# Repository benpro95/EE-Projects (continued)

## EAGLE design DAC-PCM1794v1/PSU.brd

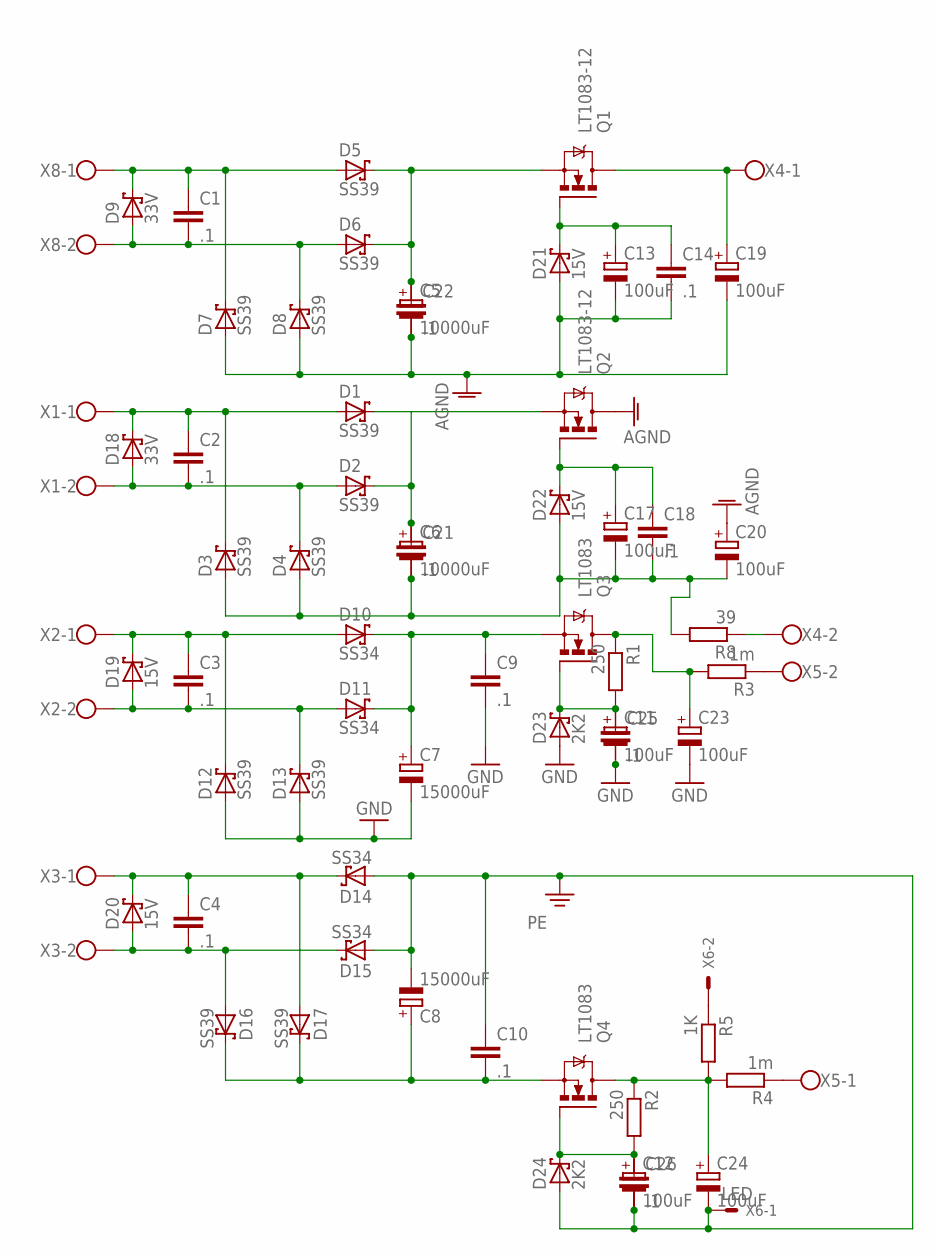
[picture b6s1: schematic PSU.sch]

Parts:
C1, C2, C3, C4: .1; C075-042X103
C5, C6: 10000uF; EB25D
C7, C8: 15000uF; EB25D
C9, C10, C14, C18, C21, C22, C25, C26: .1; C1210K
C11, C12, C13, C17, C19, C20, C23, C24: 100uF; E5-10,5
D1, D2, D3, D4, D5, D6, D7, D8, D12, D13, D16, D17: SS39; SMC
D9, D18: 33V; SMB
D10, D11, D14, D15: SS34; SMC
D19, D20, D21, D22: 15V; SMB
D23, D24: 2K2; SMB
Q1, Q2: LT1083-12; TO-247AD-H
Q3, Q4: LT1083; TO-247AD-H
R1, R2: 250; R1210
R3, R4: 1m; 0309/12
R5: 1K; R1210
R8: 39; 0309/12
X1, X2, X3, X4, X5, X8: W237-102; MPN 237-102
X6: LED; 22-23-2021

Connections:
AGND: C5.-, C13.-, C14.2, C19.-, C20.+, C22.2, D7.A, D8.A, D21.A, Q2.D
FGD: C7.-, C9.2, C11.-, C23.-, C25.2, D12.A, D13.A, D23.A
unnamed: C2.1, D1.A, D3.C, D18.C, X1.1
unnamed: C2.2, D2.A, D4.C, D18.A, X1.2
unnamed: C17.+, C18.1, D22.C, Q2.G
unnamed: C13.+, C14.1, D21.C, Q1.G
unnamed: C3.1, D10.A, D12.C, D19.C, X2.1
unnamed: C3.2, D11.A, D13.C, D19.A, X2.2
unnamed: C8.+, C10.2, D16.C, D17.C, Q4.S
unnamed: C7.+, C9.1, D10.C, D11.C, Q3.S
unnamed: C4.1, D14.C, D17.A, D20.C, X3.1
unnamed: C4.2, D15.C, D16.A, D20.A, X3.2
unnamed: C23.+, Q3.D, R1.1, R3.2
unnamed: C6.+, C21.1, D1.C, D2.C, Q2.S
unnamed: C19.+, Q1.D, X4.1
unnamed: C11.+, C25.1, D23.C, Q3.G, R1.2
unnamed: R8.1, X4.2
unnamed: C12.+, C26.1, D24.C, Q4.G, R2.2
unnamed: C24.+, Q4.D, R2.1, R4.2, R5.2
unnamed: R3.1, X5.2
unnamed: C1.1, D5.A, D7.C, D9.C, X8.1
unnamed: C1.2, D6.A, D8.C, D9.A, X8.2
unnamed: R4.1, X5.1
unnamed: C5.+, C22.1, D5.C, D6.C, Q1.S
unnamed: R5.1, X6.2
unnamed: C6.-, C17.-, C18.2, C20.-, C21.2, D3.A, D4.A, D22.A, R8.2
PE: C8.-, C10.1, C12.-, C24.-, C26.2, D14.A, D15.A, D24.A, X6.1

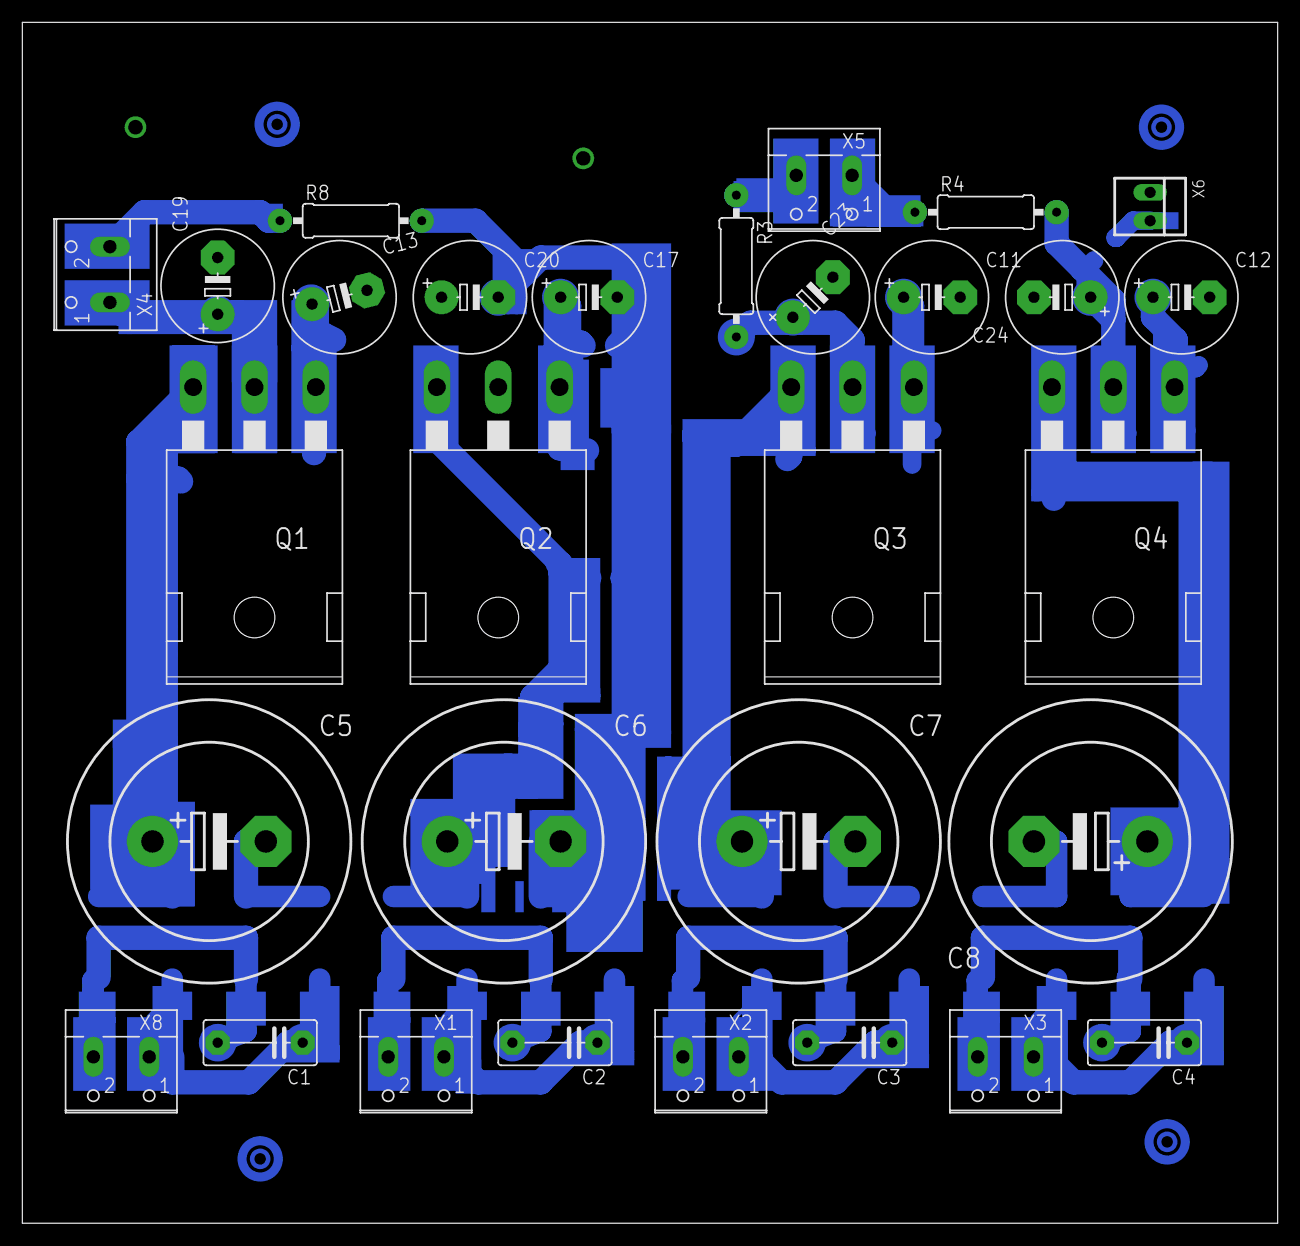
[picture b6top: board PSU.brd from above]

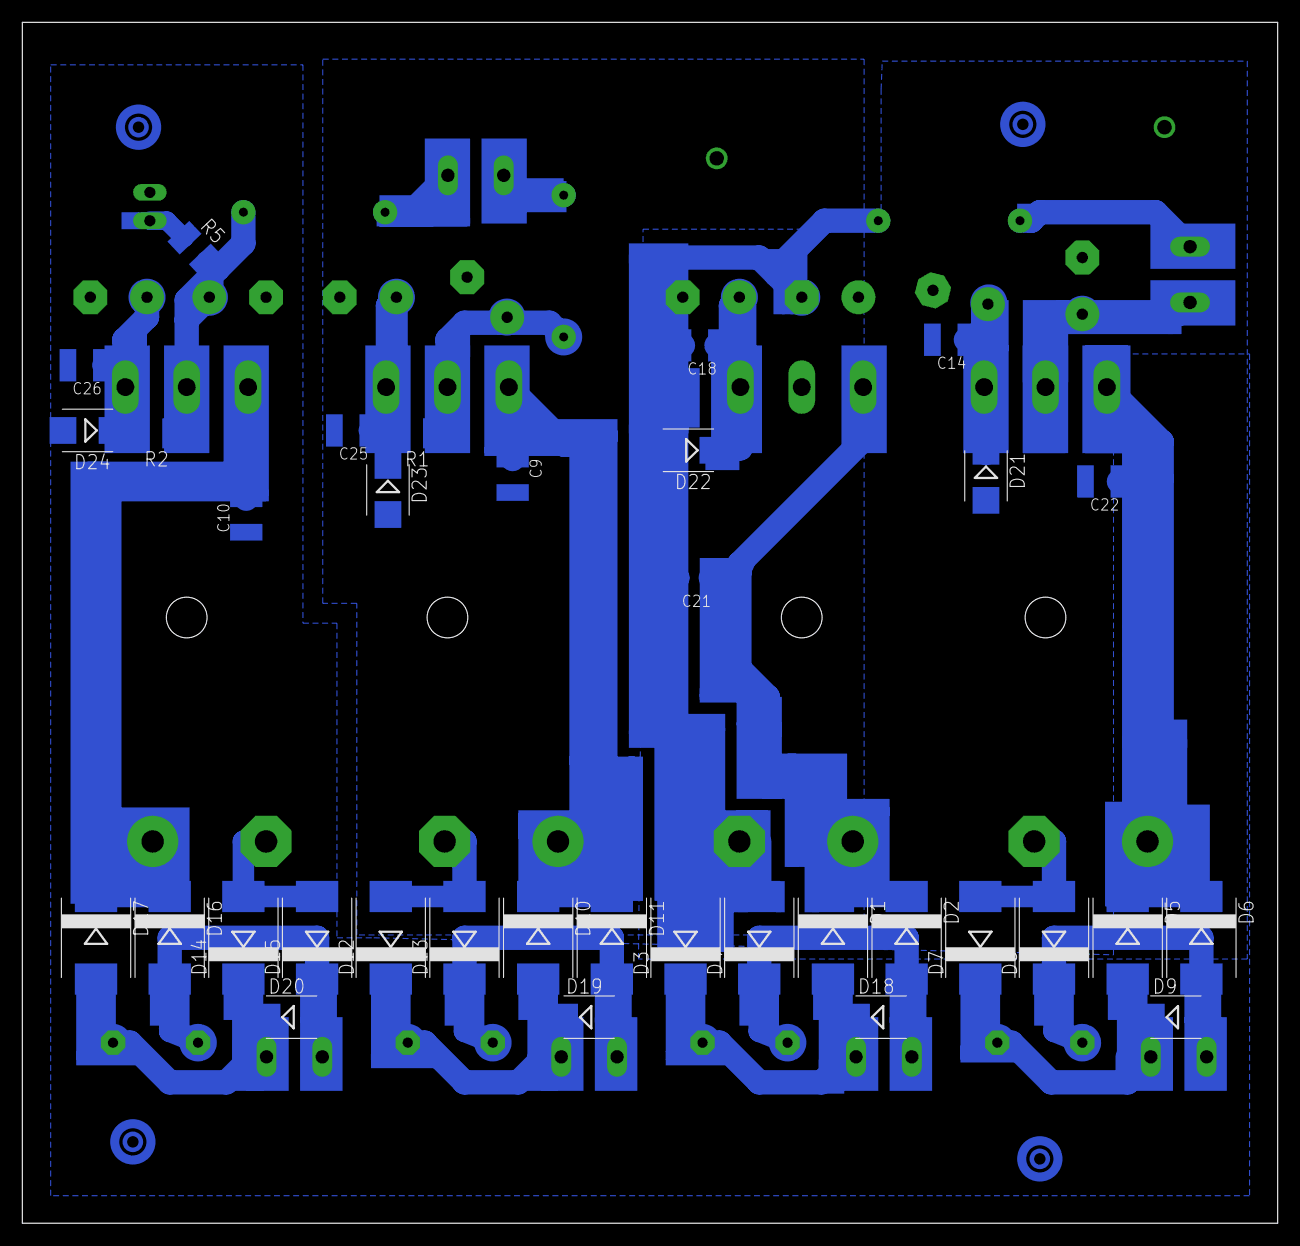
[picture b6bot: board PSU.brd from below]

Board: 2 copper layers, 112.5 x 107.6 mm, 65 parts (35 on the bottom side), 27 nets.

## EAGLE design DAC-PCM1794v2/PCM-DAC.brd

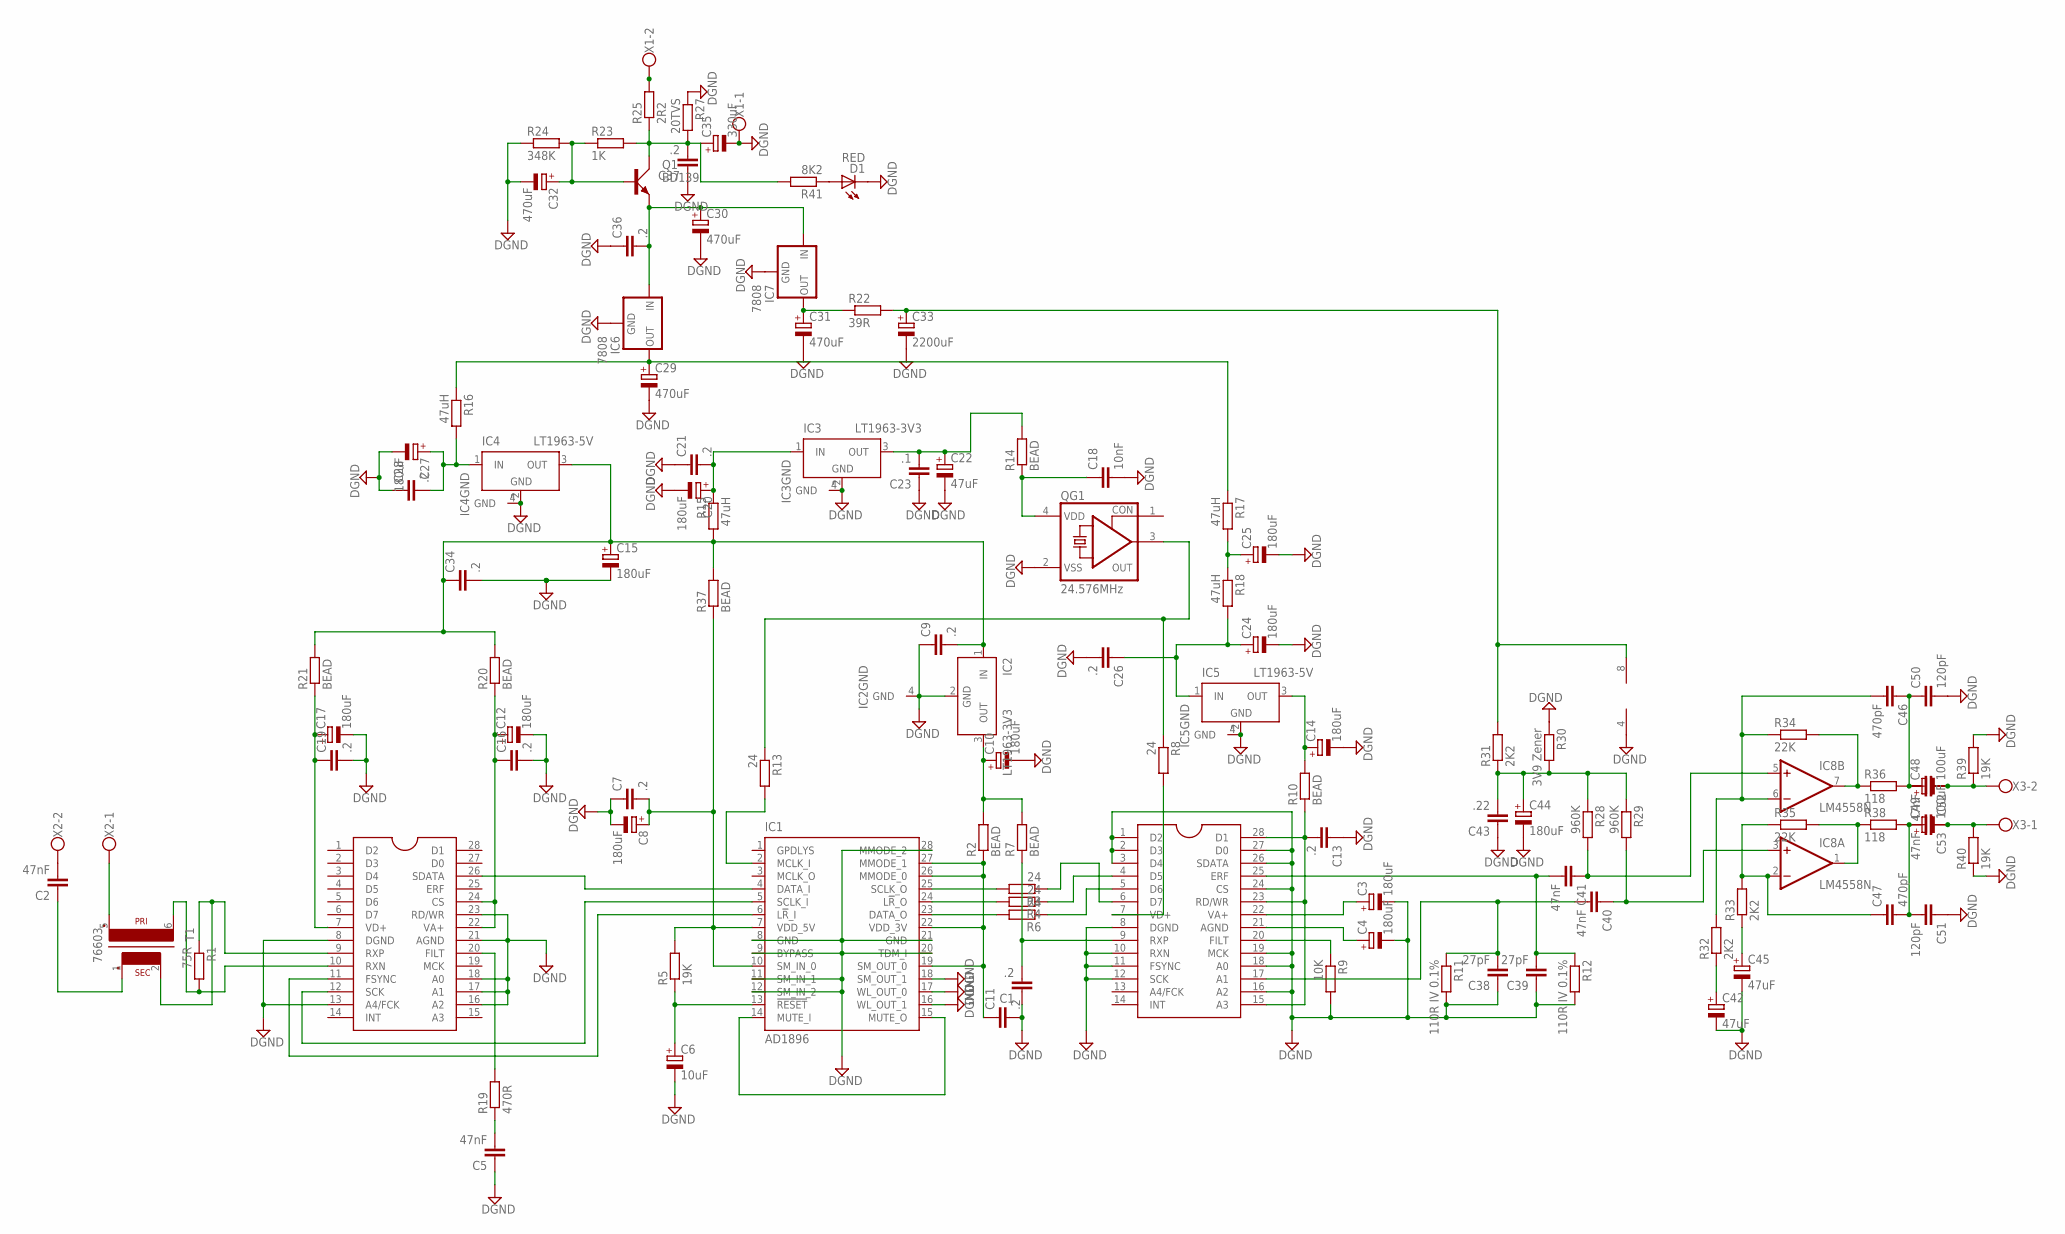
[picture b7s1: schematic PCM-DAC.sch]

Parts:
C1, C7, C9, C11, C13, C16, C19, C21, C26, C28, C34, C36, C37: .2; C1210K
C2, C5, C40, C41, C52, C53: 47nF; C050-075X075
C3, C4, C8, C10, C12, C14, C15, C17, C20, C24, C25, C27: 180uF; E3,5-8
C6: 10uF; E2,5-7
C18: 10nF; C1210K
C22, C42, C45: 47uF; E3,5-8
C23: .1; C1210K
C29, C30, C31, C32: 470uF; E5-10,5
C33: 2200uF; E7,5-16
C35: 330uF; E7,5-16
C38, C39: 27pF; C1210K
C43: .22; C1210K
C44: 180uF; E5-10,5
C46, C47: 470pF; C1210K
C48, C49: 100uF; E5-10,5
C50, C51: 120pF; C1210K
D1: RED; SFH482
IC1: AD1896; DIL28-6
IC2, IC3: LT1963-3V3; SOT223
IC4, IC5: LT1963-5V; SOT223
IC6, IC7: 7808; 78XXL
IC8: LM4558N; DIL08
Q1: BD139; TO126AV
QG1: 24.576MHz; 1100S
R1: 75R; 0309/12
R2, R7, R10, R14, R20, R21, R37: BEAD; R1210
R3, R4, R6, R8, R13: 24; R1210
R5: 19K; 0204/7
R9: 10K; R1210
R11, R12: 110R IV 0.1%; 0309/12
R15, R16, R17, R18: 47uH; 0309/12
R19: 470R; 0204/7
R22: 39R; 0309/12
R23: 1K; R1210
R24: 348K; R1210
R25: 2R2; 0309/12
R27: 20TVS; R5025
R28, R29: 960K; 0309/12
R30: 3V9 Zener; R1210
R31, R32, R33: 2K2; R1210
R34, R35: 22K; 0309/12
R36, R38: 118; 0309/12
R39, R40: 19K; 0309/12
R41: 8K2; R1210
T1: 76603; 766-4
U$1: CS8412; DIL28
U$2: PCM1794A; DIL28
X1, X2, X3: W237-02P; W237-132

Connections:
DGND: C1.1, C3.-, C4.-, C5.1, C6.-, C7.1, C8.-, C9.1, C10.-, C11.2, C12.-, C13.1, C14.-, C15.-, C16.2, C17.-, C18.2, C19.2, C20.-, C21.1, C22.-, C23.1, C24.-, C25.-, C26.2, C27.-, C28.1, C29.-, C30.-, C31.-, C32.-, C33.-, C34.2, C35.-, C36.1, C37.1, C38.1, C39.1, C42.-, C43.1, C44.-, C45.-, C50.2, C51.1, D1.K (C), IC1.8 (GND), IC1.9 (BYPASS), IC1.11 (SM_IN_1), IC1.12 (SM_IN_2), IC1.16 (WL_OUT_1), IC1.17 (WL_OUT_0), IC1.18 (SM_OUT_1), IC1.20 (TDM_I), IC1.21 (GND), IC1.28 (MMODE_2), IC2.2 (GND), IC2.4 (GND), IC3.2 (GND), IC3.4 (GND), IC4.2 (GND), IC4.4 (GND), IC5.2 (GND), IC5.4 (GND), IC6.GND, IC7.GND, IC8.4 (V-), QG1.2 (VSS), R9.2, R11.2, R12.2, R24.1, R27.1, R30.1, R39.2, R40.1, U$1.8 (DGND), U$1.13 (A4/FCK), U$1.16 (A2), U$1.17 (A1), U$1.18 (A0), U$1.21 (AGND), U$1.23 (RD/WR), U$2.1 (D2), U$2.2 (D3), U$2.3 (D4), U$2.8 (DGND), U$2.10 (RXN), U$2.11 (FSYNC), U$2.12 (SCK), U$2.16 (A2), U$2.18 (A0), U$2.19 (MCK), U$2.24 (CS), U$2.26 (SDATA), U$2.27 (D0), X1.1
unnamed: C2.2, X2.2
unnamed: IC1.14 (MUTE_I), IC1.15 (MUTE_O)
unnamed: T1.5 (P1), X2.1
unnamed: C2.1, T1.1 (S1)
unnamed: IC1.4 (DATA_I), U$1.26 (SDATA)
unnamed: IC1.5 (SCLK_I), U$1.12 (SCK)
unnamed: IC1.6 (L!R!_I), U$1.11 (FSYNC)
unnamed: C11.1, IC1.19 (SM_OUT_0), IC1.22 (VDD_3V), IC1.26 (MMODE_0), IC1.27 (MMODE_1), R2.1
unnamed: C7.2, C8.+, IC1.7 (VDD_5V), IC1.10 (SM_IN_0), R5.2, R37.1
unnamed: C10.+, IC2.3 (OUT), R2.2, R7.2
unnamed: C9.2, C15.+, C34.1, IC2.1 (IN), IC4.3 (OUT), R15.2, R20.2, R21.2, R37.2
unnamed: IC1.23 (DATA_O), R6.2
unnamed: IC1.24 (L!R!_O), R4.2
unnamed: IC1.25 (SCLK_O), R3.2
unnamed: R4.1, U$2.4 (D5)
unnamed: R6.1, U$2.5 (D6)
unnamed: R3.1, U$2.6 (D7)
unnamed: C1.2, R7.1, U$2.9 (RXP)
unnamed: C13.2, R10.1, U$2.15 (A3), U$2.23 (RD/WR), U$2.28 (D1)
unnamed: R8.2, U$2.7 (VD+)
unnamed: R9.1, U$2.20 (FILT)
unnamed: C3.+, U$2.22 (VA+)
unnamed: C4.+, U$2.21 (AGND)
unnamed: C14.+, IC5.3 (OUT), R10.2
unnamed: C39.2, C41.2, R12.1, U$2.25 (ERF)
unnamed: C38.2, C40.2, R11.1, U$2.17 (A1)
unnamed: IC1.2 (MCLK_I), R13.2
unnamed: QG1.3 (OUT), R8.1, R13.1
unnamed: C20.+, C21.2, IC3.1 (IN), R15.1
unnamed: C18.1, QG1.4 (VDD), R14.1
unnamed: C22.+, C23.2, IC3.3 (OUT), R14.2
unnamed: C27.+, C28.2, IC4.1 (IN), R16.2
unnamed: C29.+, IC6.OUT, R16.1, R17.1
unnamed: C24.+, C26.1, IC5.1 (IN), R18.2
unnamed: C25.+, R17.2, R18.1
unnamed: C30.+, C36.2, IC6.IN, IC7.IN, Q1.E
unnamed: C31.+, IC7.OUT, R22.1
unnamed: C33.+, IC8.8 (V+), R22.2, R31.2
unnamed: R25.2, X1.2
unnamed: C32.+, Q1.B, R23.1, R24.2
unnamed: C35.+, C37.2, Q1.C, R23.2, R25.1, R27.2, R41.2
unnamed: C41.1, IC8.5 (+IN), R28.2
unnamed: C40.1, IC8.3 (+IN), R29.2
unnamed: C43.2, C44.+, R28.1, R29.1, R30.2, R31.1
unnamed: IC8.1 (OUT), R35.2, R38.1
unnamed: C47.1, IC8.2 (-IN), R33.2, R35.1
unnamed: C46.2, IC8.6 (-IN), R32.2, R34.1
unnamed: C42.+, R32.1
unnamed: C45.+, R33.1
unnamed: IC8.7 (OUT), R34.2, R36.1
unnamed: C46.1, C48.+, C50.1, C52.2, R36.2
unnamed: C47.2, C49.+, C51.2, C53.2, R38.2
unnamed: R1.2, T1.6 (P2), U$1.10 (RXN)
unnamed: C48.-, C52.1, R39.1, X3.2
unnamed: C49.-, C53.1, R40.2, X3.1
unnamed: D1.A, R41.1
unnamed: R1.1, T1.2 (S2), U$1.9 (RXP)
unnamed: C17.+, C19.1, R21.1, U$1.7 (VD+)
unnamed: C12.+, C16.1, R20.1, U$1.22 (VA+), U$1.24 (CS)
unnamed: C5.2, R19.1
unnamed: R19.2, U$1.20 (FILT)
unnamed: C6.+, IC1.13 (!RESET), R5.1

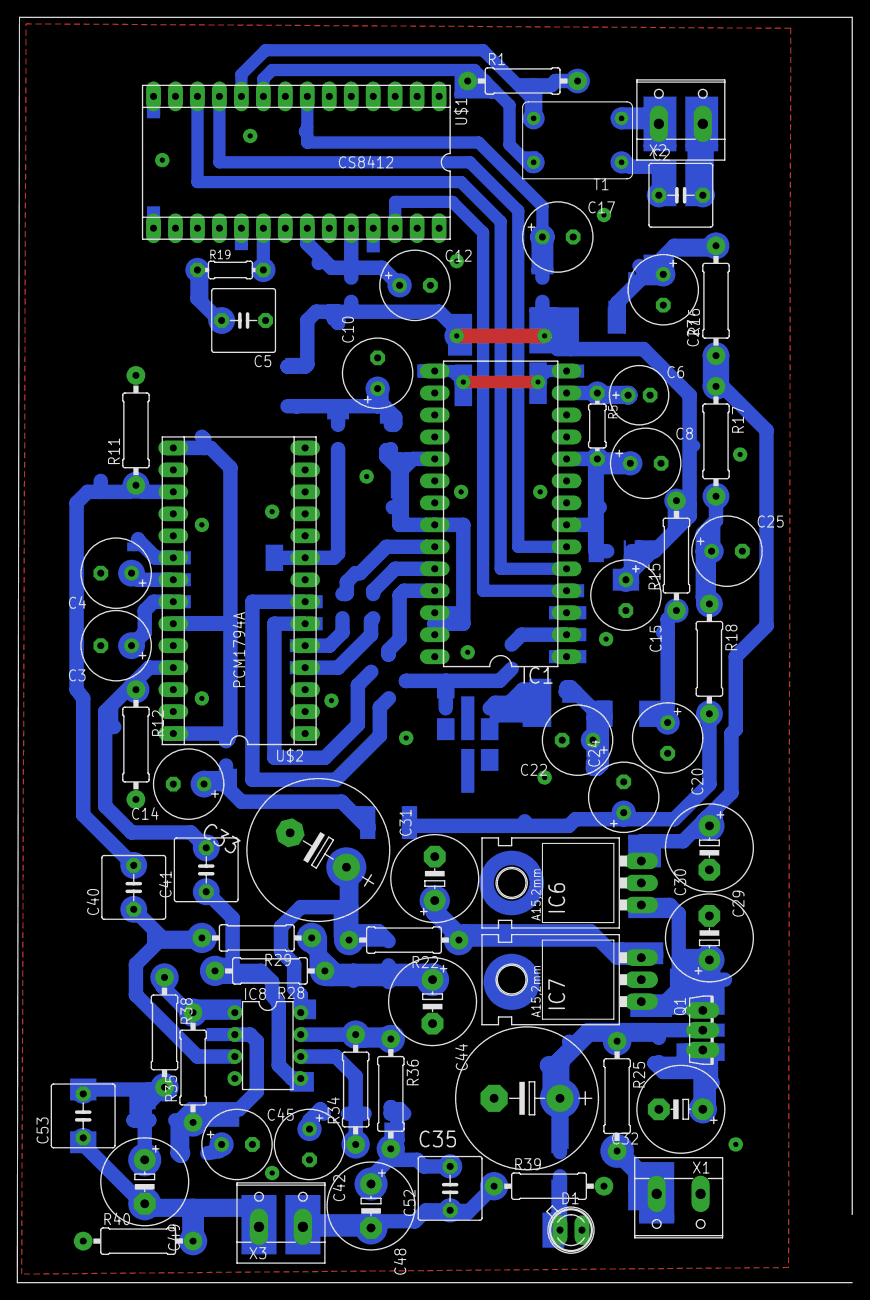
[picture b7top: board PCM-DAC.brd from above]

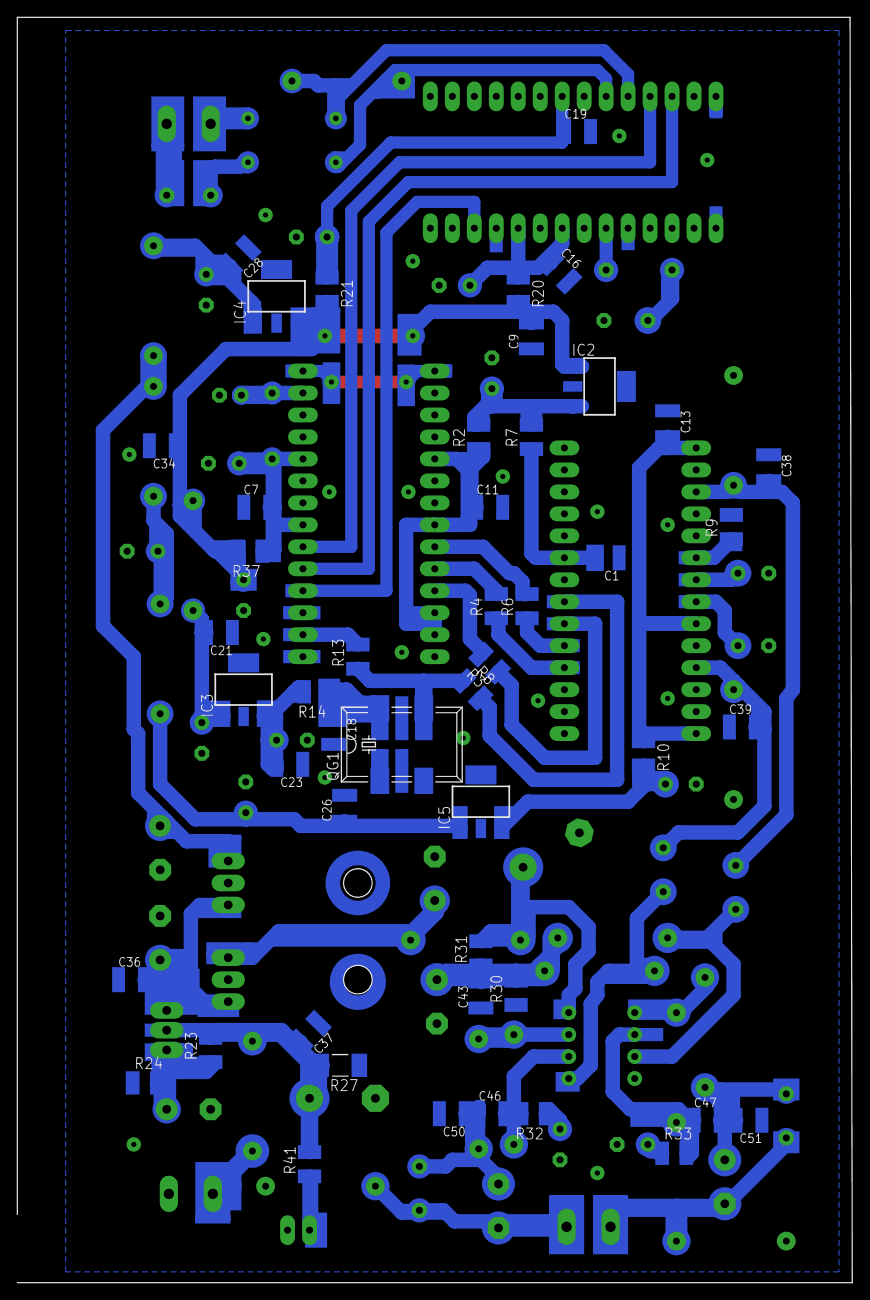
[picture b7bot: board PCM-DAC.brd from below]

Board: 2 copper layers, 96.5 x 146.3 mm, 110 parts (48 on the bottom side), 63 nets.
